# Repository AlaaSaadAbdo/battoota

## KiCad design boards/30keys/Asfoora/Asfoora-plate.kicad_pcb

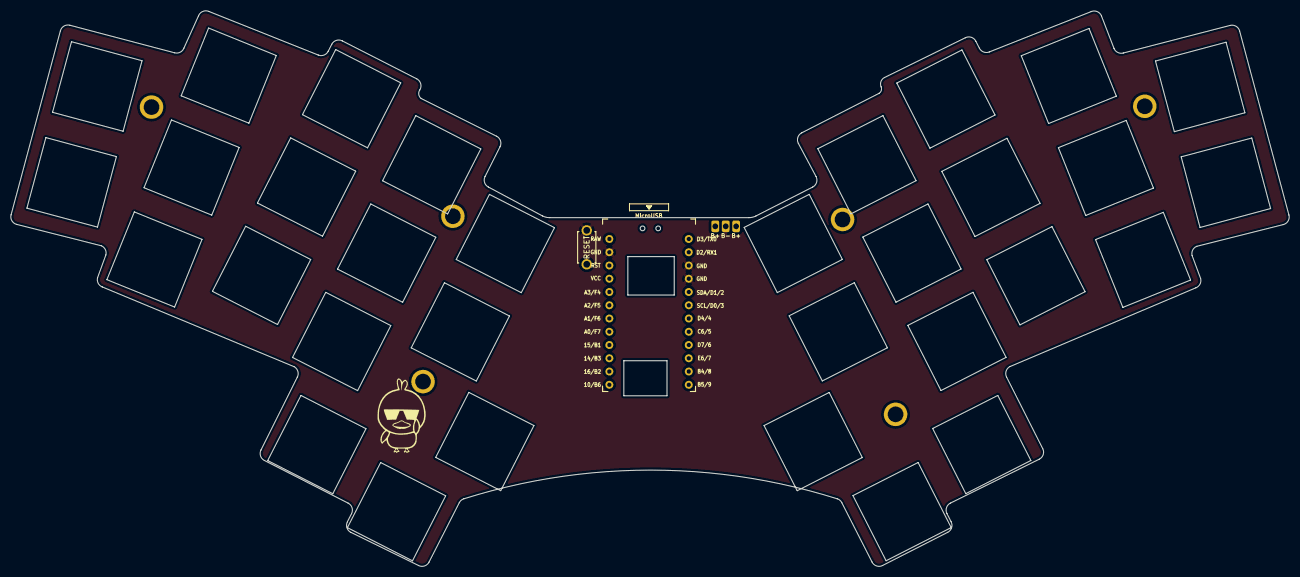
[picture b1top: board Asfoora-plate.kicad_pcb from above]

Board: 2 copper layers, 245.0 x 106.5 mm, 36 parts (1 on the bottom side), 4 nets, no tracks yet.

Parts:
PAD1: bat
SW1, SW16: Rotary_Encoder_Switch; 14mm-switch-hole
SW2, SW3, SW4, SW5, SW6, SW7, SW8, SW9, SW10, SW11, SW12, SW13, SW14, SW15, SW17, SW18, SW19, SW20, SW21, SW22, SW23, SW24, SW25, SW26, SW27, SW28, SW29, SW30, SW31, SW32: SW_Push; 14mm-switch-hole
SW33: SW_Push; ResetSW
SW34: SW_SPDT; SW_SPDT_PCM12
U1: ProMicro_r; ProMicro_v3.5

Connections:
bat+: PAD1.1, PAD1.3, SW34.2 (B)
gnd: PAD1.2, SW33.2, U1.3 (GND), U1.4 (GND), U1.23 (GND)
raw: SW34.3 (C), U1.24 (RAW)
reset: SW33.1, U1.22 (RST)

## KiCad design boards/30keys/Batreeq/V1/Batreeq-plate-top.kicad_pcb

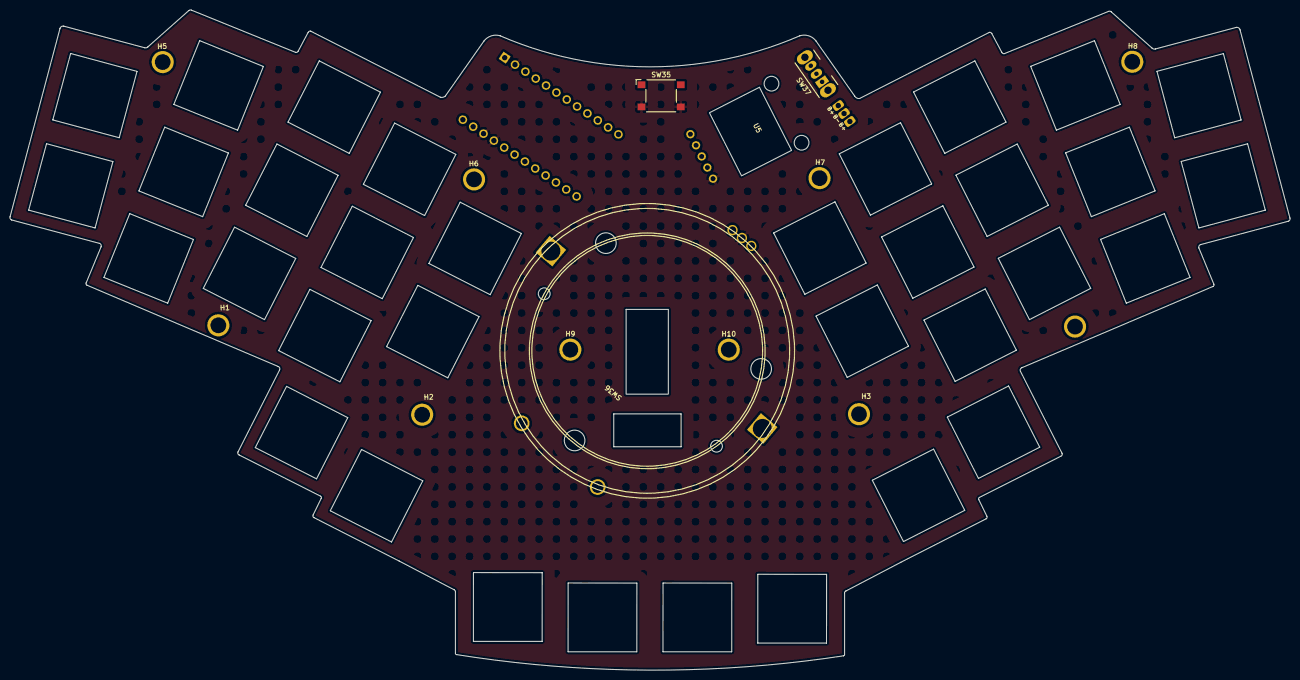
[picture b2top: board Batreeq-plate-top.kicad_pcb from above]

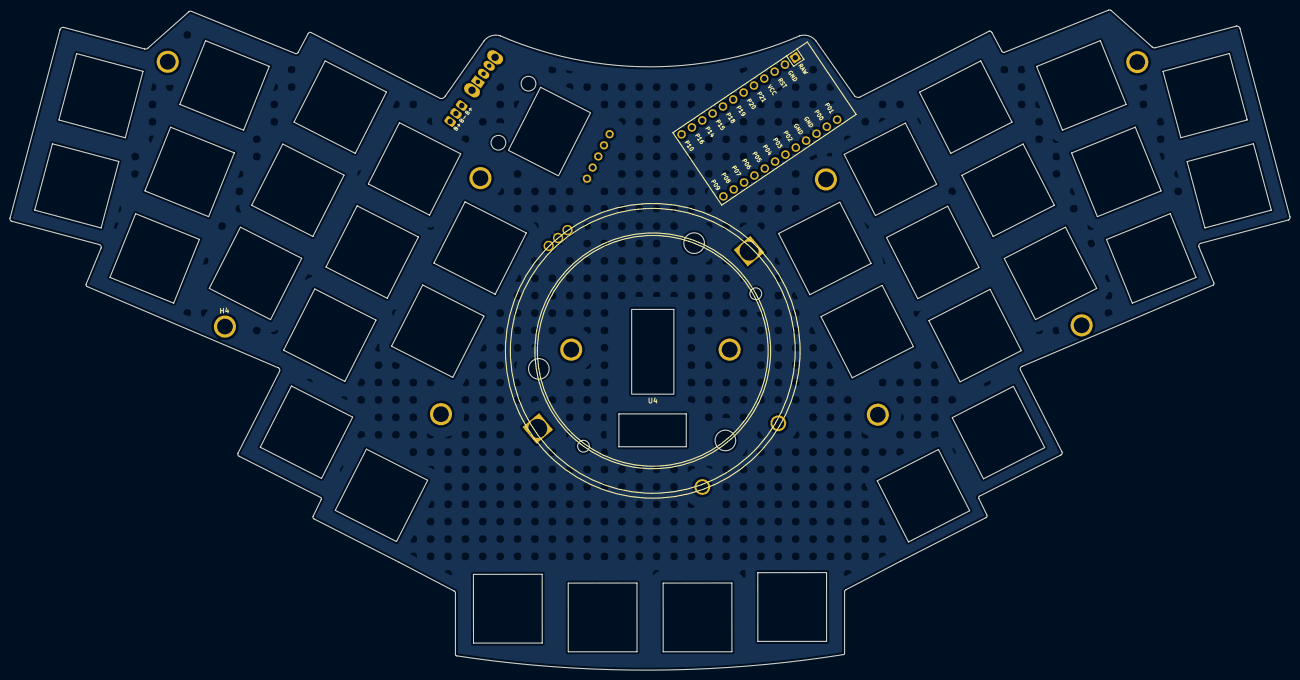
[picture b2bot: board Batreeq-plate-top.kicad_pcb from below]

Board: 2 copper layers, 260.7 x 134.4 mm, 51 parts (2 on the bottom side), 9 nets, no tracks yet.

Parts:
H1, H2, H3, H4, H5, H6, H7, H8, H9, H10: MountingHole_Pad; MountingHole_M3
PAD1: bat
SW1, SW2, SW3, SW4, SW5, SW6, SW7, SW8, SW9, SW10, SW11, SW12, SW13, SW14, SW15, SW16, SW17, SW18, SW19, SW20, SW21, SW22, SW23, SW24, SW25, SW26, SW27, SW28, SW29, SW30, SW31, SW32, SW33, SW34: SW_Push; 14mm-switch-hole
SW35: SW_Push; SW_SPST_Omron_B3FS-100xP
SW36: RotaryEncoder; PERS56v2
SW37: SW_SPDT; SW_CuK_OS102011MA1QN1_SPDT_Angled
U1: ProMicro_r; ProMicro2
U4: PMW3360DM-T2QU
U5: DRV2605L; Pimoroni Haptic Buzz DRV2605L Driver

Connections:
EncL: SW36.A, U1.20 (A3/F4)
EncR: SW36.B, U1.19 (A2/F5)
GND: PAD1.2, SW35.2, SW36.C, U1.3 (GND), U1.4 (GND), U1.23 (GND), U5.5 (GND)
RAW: SW37.3 (C), U1.24 (RAW)
RESET: SW35.1, U1.22 (RST)
SCL: U1.6 (SCL/D0/3), U5.3 (SCL)
SDA: U1.5 (SDA/D1/2), U5.2 (SDA)
VCC: U1.21 (VCC), U5.1 (VDD)
bat+: PAD1.1, PAD1.3, SW37.2 (B)

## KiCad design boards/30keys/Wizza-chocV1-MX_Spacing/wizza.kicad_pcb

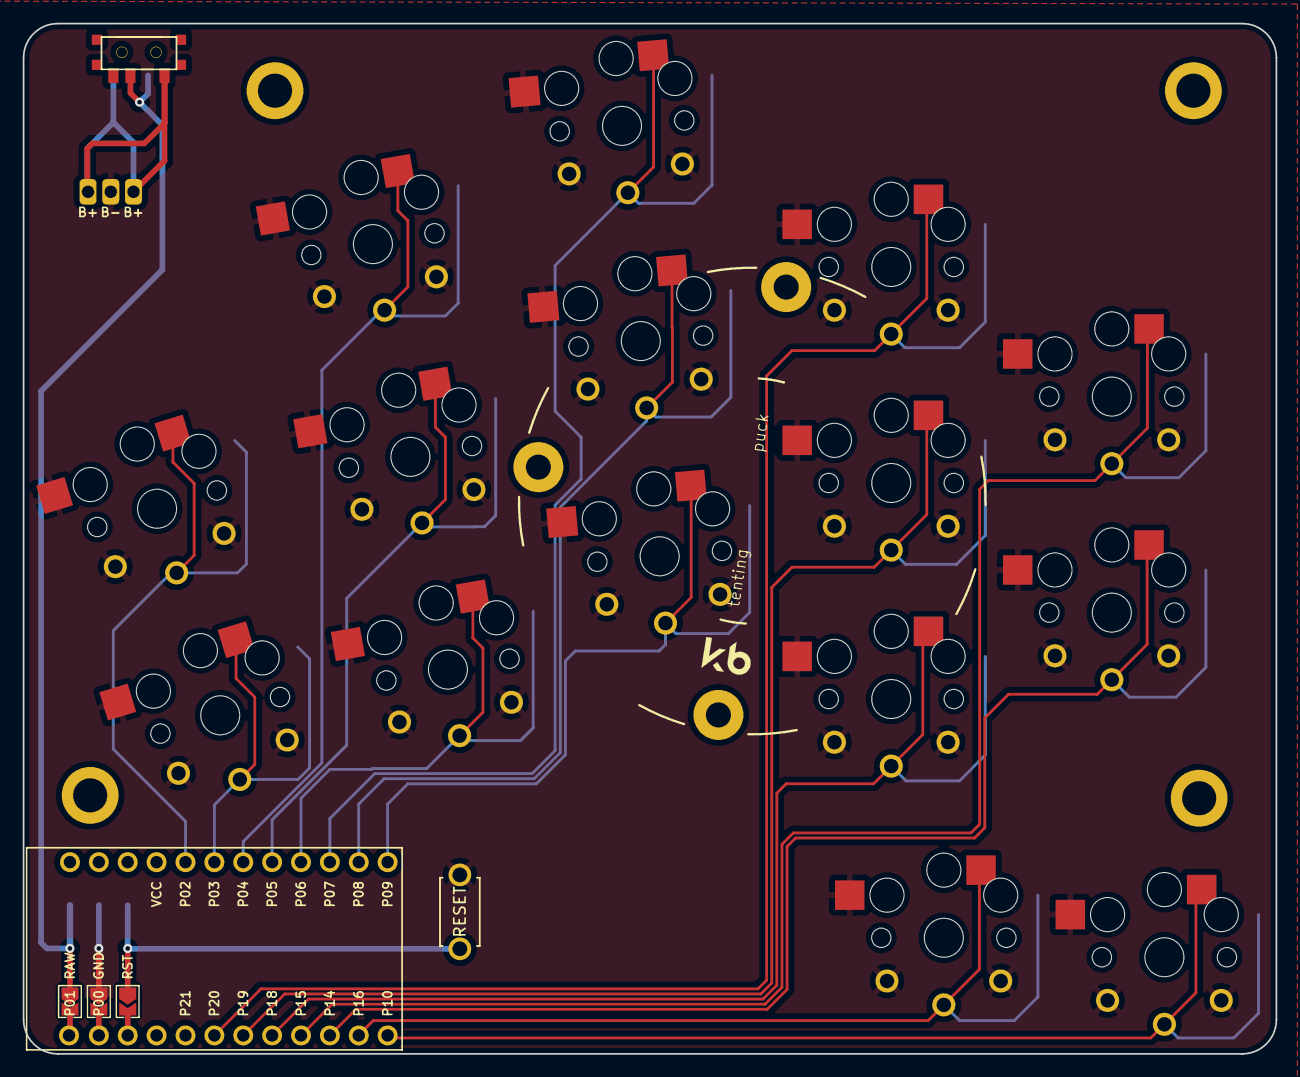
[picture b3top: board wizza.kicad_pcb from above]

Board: 2 copper layers, 110.2 x 90.6 mm, 20 parts (0 on the bottom side), 19 nets.

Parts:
B1: ResetSW
MCU1: ProMicro32keys
PAD1: bat
S1, S2, S3, S4, S5, S6, S7, S8, S9, S10, S11, S12, S13, S14, S15: key
T1, T2: SPDT_C128955

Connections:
GND: B1.2, MCU1.2, PAD1.2, S1.1, S2.1, S3.1, S4.1, S5.1, S6.1, S7.1, S8.1, S9.1, S10.1, S11.1, S12.1, S13.1, S14.1, S15.1
RAW: MCU1.1, T1.2, T2.2
RST: B1.1, MCU1.3
b+: PAD1.1, PAD1.3, T1.1, T2.1
matrix_index_bottom: MCU1.8, S9.2
matrix_index_home: MCU1.7, S10.2
matrix_index_top: MCU1.6, S11.2
matrix_inner_bottom: MCU1.10, S12.2
matrix_inner_home: MCU1.9, S13.2
matrix_middle_bottom: MCU1.24, S6.2
matrix_middle_home: MCU1.23, S7.2
matrix_middle_top: MCU1.22, S8.2
matrix_pinky_home: MCU1.18, S1.2
matrix_pinky_top: MCU1.17, S2.2
matrix_ring_bottom: MCU1.21, S3.2
matrix_ring_home: MCU1.20, S4.2
matrix_ring_top: MCU1.19, S5.2
thumb_reachy: MCU1.12, S15.2
thumb_tucky: MCU1.11, S14.2

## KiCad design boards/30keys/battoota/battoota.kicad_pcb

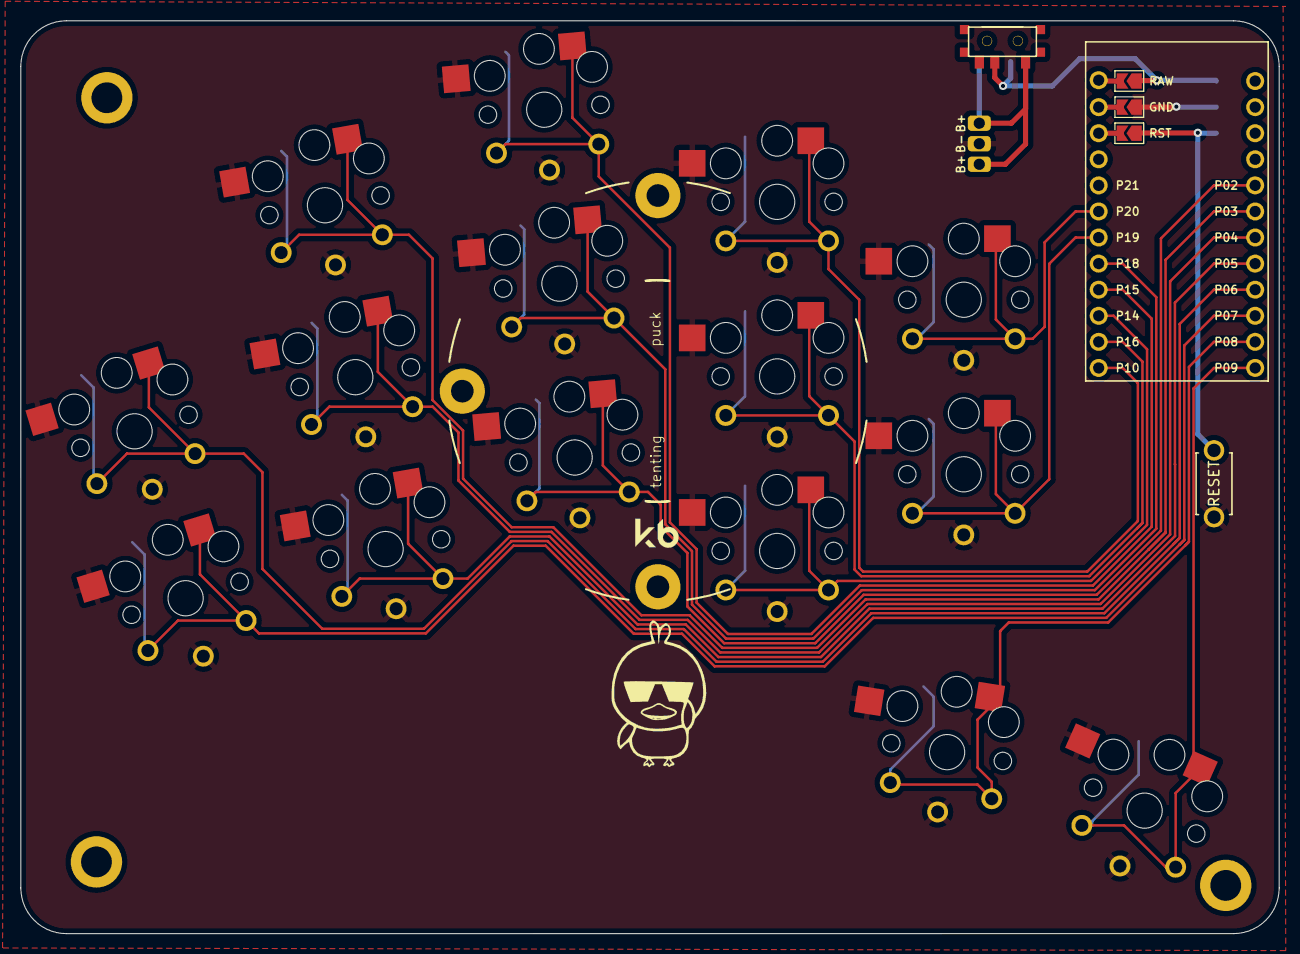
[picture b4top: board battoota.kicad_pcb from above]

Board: 2 copper layers, 122.6 x 88.9 mm, 20 parts (0 on the bottom side), 19 nets.

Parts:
B1: ResetSW
MCU1: ProMicro
PAD1: bat
S3, S5, S7, S9, S11, S13, S15, S17, S19, S21, S23, S27, S29, S31, S33: choc_hotswap_key
T1, T2: SPDT_C128955

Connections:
Braw: PAD1.1, PAD1.3, T1.1, T2.1
GND: B1.2, MCU1.2, PAD1.2, S3.2, S5.2, S7.2, S9.2, S11.2, S13.2, S15.2, S17.2, S19.2, S21.2, S23.2, S27.2, S29.2, S31.2, S33.2
P2: MCU1.17, S13.1
P3: MCU1.18, S11.1
P4: MCU1.19, S9.1
P5: MCU1.20, S7.1
P6: MCU1.21, S5.1
P7: MCU1.22, S3.1
P8: MCU1.23, S31.1
P9: MCU1.24, S33.1
P10: MCU1.12, S23.1
P14: MCU1.10, S19.1
P15: MCU1.9, S17.1
P16: MCU1.11, S21.1
P18: MCU1.8, S15.1
P19: MCU1.7, S27.1
P20: MCU1.6, S29.1
RAW: MCU1.1, T1.2, T2.2
RST: B1.1, MCU1.3
